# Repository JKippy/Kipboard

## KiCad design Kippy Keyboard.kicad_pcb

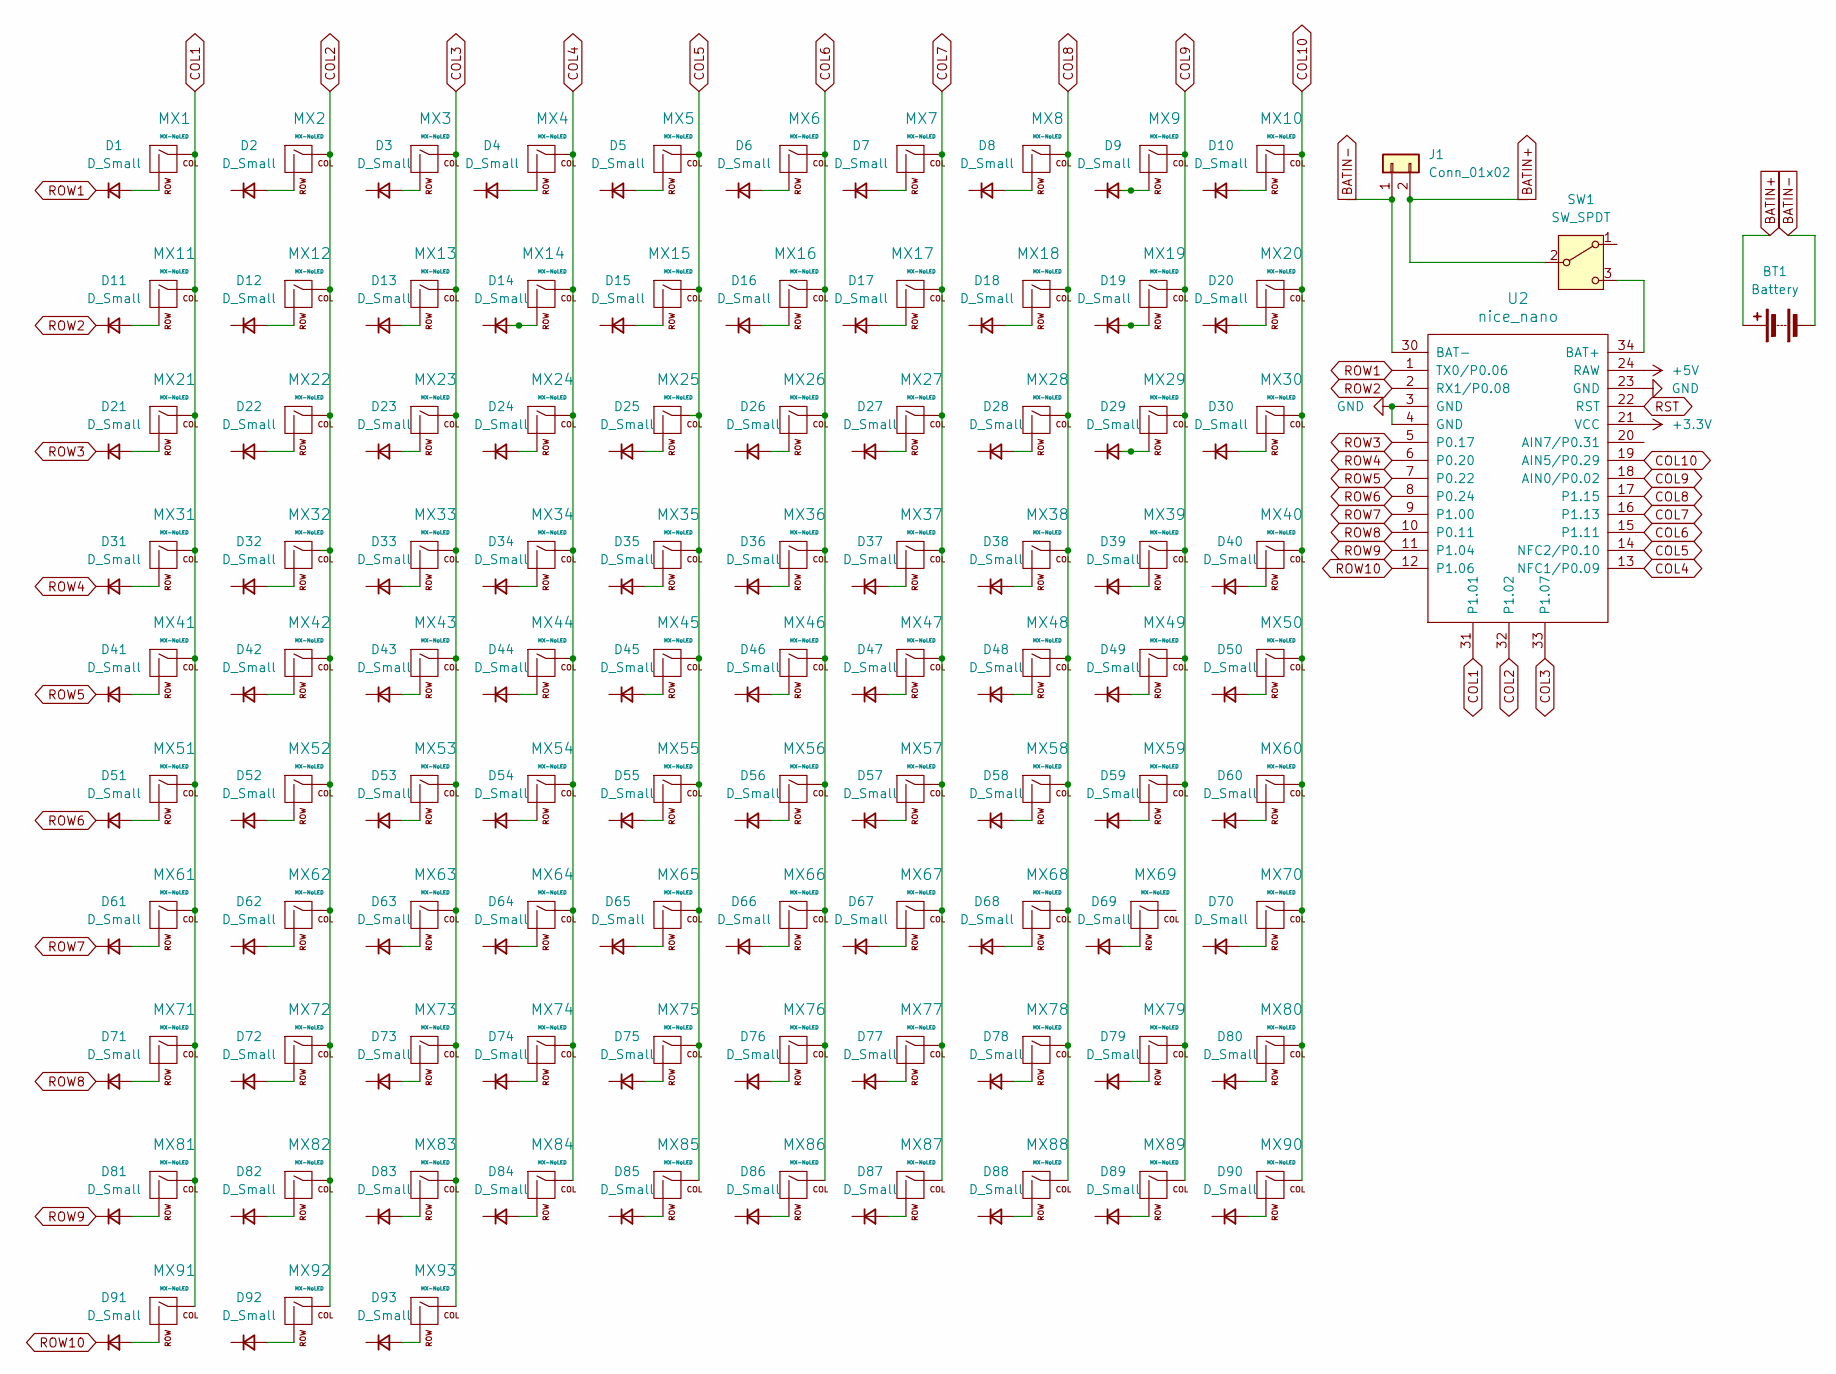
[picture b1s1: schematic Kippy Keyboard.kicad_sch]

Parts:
BT1: Battery
D1, D2, D3, D4, D5, D6, D7, D8, D9, D10, D11, D12, D13, D14, D15, D16, D17, D18, D19, D20, D21, D22, D23, D24, D25, D26, D27, D28, D29, D30, D31, D32, D33, D34, D35, D36, D37, D38, D39, D40, D41, D42, D43, D44, D45, D46, D47, D48, D49, D50, D51, D52, D53, D54, D55, D56, D57, D58, D59, D60, D61, D62, D63, D64, D65, D66, D67, D68, D69, D70, D71, D72, D73, D74, D75, D76, D77, D78, D79, D80, D81, D82, D83, D84, D85, D86, D87, D88, D89, D90, D91, D92, D93: D_Small; D_SOD-123
J1: Conn_01x02; JST_PH_S2B-PH-K_1x02_P2.00mm_Horizontal
MX1, MX2, MX3, MX4, MX5, MX6, MX7, MX8, MX9, MX10, MX11, MX12, MX13, MX14, MX15, MX16, MX17, MX18, MX19, MX20, MX21, MX22, MX23, MX24, MX25, MX26, MX27, MX28, MX29, MX30, MX31, MX32, MX33, MX34, MX35, MX36, MX37, MX38, MX39, MX40, MX41, MX42, MX43, MX44, MX45, MX46, MX47, MX48, MX49, MX50, MX51, MX52, MX53, MX54, MX55, MX56, MX57, MX58, MX59, MX60, MX61, MX62, MX63, MX64, MX65, MX66, MX67, MX68, MX69, MX70, MX71, MX72, MX73, MX74, MX75, MX76, MX77, MX78, MX79, MX80, MX81, MX82, MX83, MX84, MX85, MX86, MX87, MX88, MX89, MX90, MX91, MX92, MX93: MX-NoLED; SW_Hotswap_Kailh_MX_1.00u_3d; MPN CPG151101S11-16
SW1: SW_SPDT; SW_Slide_SPDT_Angled_CK_OS102011MA1Q
U2: nice_nano

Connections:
+3.3V: U2.21 (VCC)
+5V: U2.24 (RAW)
BATIN+: BT1.1 (+), J1.2, SW1.2 (B)
BATIN-: BT1.2 (-), J1.1, U2.30 (BAT-)
COL1: MX1.1 (COL), MX11.1 (COL), MX21.1 (COL), MX31.1 (COL), MX41.1 (COL), MX51.1 (COL), MX61.1 (COL), MX71.1 (COL), MX81.1 (COL), MX91.1 (COL), U2.31 (P1.01)
COL2: MX2.1 (COL), MX12.1 (COL), MX22.1 (COL), MX32.1 (COL), MX42.1 (COL), MX52.1 (COL), MX62.1 (COL), MX72.1 (COL), MX82.1 (COL), MX92.1 (COL), U2.32 (P1.02)
COL3: MX3.1 (COL), MX13.1 (COL), MX23.1 (COL), MX33.1 (COL), MX43.1 (COL), MX53.1 (COL), MX63.1 (COL), MX73.1 (COL), MX83.1 (COL), MX93.1 (COL), U2.33 (P1.07)
COL4: MX4.1 (COL), MX14.1 (COL), MX24.1 (COL), MX34.1 (COL), MX44.1 (COL), MX54.1 (COL), MX64.1 (COL), MX74.1 (COL), MX84.1 (COL), U2.13 (NFC1/P0.09)
COL5: MX5.1 (COL), MX15.1 (COL), MX25.1 (COL), MX35.1 (COL), MX45.1 (COL), MX55.1 (COL), MX65.1 (COL), MX75.1 (COL), MX85.1 (COL), U2.14 (NFC2/P0.10)
COL6: MX6.1 (COL), MX16.1 (COL), MX26.1 (COL), MX36.1 (COL), MX46.1 (COL), MX56.1 (COL), MX66.1 (COL), MX76.1 (COL), MX86.1 (COL), U2.15 (P1.11)
COL7: MX7.1 (COL), MX17.1 (COL), MX27.1 (COL), MX37.1 (COL), MX47.1 (COL), MX57.1 (COL), MX67.1 (COL), MX77.1 (COL), MX87.1 (COL), U2.16 (P1.13)
COL8: MX8.1 (COL), MX18.1 (COL), MX28.1 (COL), MX38.1 (COL), MX48.1 (COL), MX58.1 (COL), MX68.1 (COL), MX78.1 (COL), MX88.1 (COL), U2.17 (P1.15)
COL9: MX9.1 (COL), MX19.1 (COL), MX29.1 (COL), MX39.1 (COL), MX49.1 (COL), MX59.1 (COL), MX79.1 (COL), MX89.1 (COL), U2.18 (AIN0/P0.02)
COL10: MX10.1 (COL), MX20.1 (COL), MX30.1 (COL), MX40.1 (COL), MX50.1 (COL), MX60.1 (COL), MX70.1 (COL), MX80.1 (COL), MX90.1 (COL), U2.19 (AIN5/P0.29)
GND: U2.3 (GND), U2.4 (GND), U2.23 (GND)
unnamed: D1.2 (A), MX1.2 (ROW)
unnamed: D2.2 (A), MX2.2 (ROW)
unnamed: D3.2 (A), MX3.2 (ROW)
unnamed: D4.2 (A), MX4.2 (ROW)
unnamed: D5.2 (A), MX5.2 (ROW)
unnamed: D6.2 (A), MX6.2 (ROW)
unnamed: D7.2 (A), MX7.2 (ROW)
unnamed: D8.2 (A), MX8.2 (ROW)
unnamed: D9.2 (A), MX9.2 (ROW)
unnamed: D10.2 (A), MX10.2 (ROW)
unnamed: D11.2 (A), MX11.2 (ROW)
unnamed: D12.2 (A), MX12.2 (ROW)
unnamed: D13.2 (A), MX13.2 (ROW)
unnamed: D14.2 (A), MX14.2 (ROW)
unnamed: D15.2 (A), MX15.2 (ROW)
unnamed: D16.2 (A), MX16.2 (ROW)
unnamed: D17.2 (A), MX17.2 (ROW)
unnamed: D18.2 (A), MX18.2 (ROW)
unnamed: D19.2 (A), MX19.2 (ROW)
unnamed: D20.2 (A), MX20.2 (ROW)
unnamed: D21.2 (A), MX21.2 (ROW)
unnamed: D22.2 (A), MX22.2 (ROW)
unnamed: D23.2 (A), MX23.2 (ROW)
unnamed: D24.2 (A), MX24.2 (ROW)
unnamed: D25.2 (A), MX25.2 (ROW)
unnamed: D26.2 (A), MX26.2 (ROW)
unnamed: D27.2 (A), MX27.2 (ROW)
unnamed: D28.2 (A), MX28.2 (ROW)
unnamed: D29.2 (A), MX29.2 (ROW)
unnamed: D30.2 (A), MX30.2 (ROW)
unnamed: D31.2 (A), MX31.2 (ROW)
unnamed: D32.2 (A), MX32.2 (ROW)
unnamed: D33.2 (A), MX33.2 (ROW)
unnamed: D34.2 (A), MX34.2 (ROW)
unnamed: D35.2 (A), MX35.2 (ROW)
unnamed: D36.2 (A), MX36.2 (ROW)
unnamed: D37.2 (A), MX37.2 (ROW)
unnamed: D38.2 (A), MX38.2 (ROW)
unnamed: D39.2 (A), MX39.2 (ROW)
unnamed: D40.2 (A), MX40.2 (ROW)
unnamed: D41.2 (A), MX41.2 (ROW)
unnamed: D42.2 (A), MX42.2 (ROW)
unnamed: D43.2 (A), MX43.2 (ROW)
unnamed: D44.2 (A), MX44.2 (ROW)
unnamed: D45.2 (A), MX45.2 (ROW)
unnamed: D46.2 (A), MX46.2 (ROW)
unnamed: D47.2 (A), MX47.2 (ROW)
unnamed: D48.2 (A), MX48.2 (ROW)
unnamed: D49.2 (A), MX49.2 (ROW)
unnamed: D50.2 (A), MX50.2 (ROW)
unnamed: D51.2 (A), MX51.2 (ROW)
unnamed: D52.2 (A), MX52.2 (ROW)
unnamed: D53.2 (A), MX53.2 (ROW)
unnamed: D54.2 (A), MX54.2 (ROW)
unnamed: D55.2 (A), MX55.2 (ROW)
unnamed: D56.2 (A), MX56.2 (ROW)
unnamed: D57.2 (A), MX57.2 (ROW)
unnamed: D58.2 (A), MX58.2 (ROW)
unnamed: D59.2 (A), MX59.2 (ROW)
unnamed: D60.2 (A), MX60.2 (ROW)
unnamed: D61.2 (A), MX61.2 (ROW)
unnamed: D62.2 (A), MX62.2 (ROW)
unnamed: D63.2 (A), MX63.2 (ROW)
unnamed: D64.2 (A), MX64.2 (ROW)
unnamed: D65.2 (A), MX65.2 (ROW)
unnamed: D66.2 (A), MX66.2 (ROW)
unnamed: D67.2 (A), MX67.2 (ROW)
unnamed: D68.2 (A), MX68.2 (ROW)
unnamed: D69.2 (A), MX69.2 (ROW)
unnamed: D70.2 (A), MX70.2 (ROW)
unnamed: D71.2 (A), MX71.2 (ROW)
unnamed: D72.2 (A), MX72.2 (ROW)
unnamed: D73.2 (A), MX73.2 (ROW)
unnamed: D74.2 (A), MX74.2 (ROW)
unnamed: D75.2 (A), MX75.2 (ROW)
unnamed: D76.2 (A), MX76.2 (ROW)
unnamed: D77.2 (A), MX77.2 (ROW)
unnamed: D78.2 (A), MX78.2 (ROW)
unnamed: D79.2 (A), MX79.2 (ROW)
unnamed: D80.2 (A), MX80.2 (ROW)
unnamed: D81.2 (A), MX81.2 (ROW)
unnamed: D82.2 (A), MX82.2 (ROW)
unnamed: D83.2 (A), MX83.2 (ROW)
unnamed: D84.2 (A), MX84.2 (ROW)
unnamed: D85.2 (A), MX85.2 (ROW)
unnamed: D86.2 (A), MX86.2 (ROW)
unnamed: D87.2 (A), MX87.2 (ROW)
unnamed: D88.2 (A), MX88.2 (ROW)
unnamed: D89.2 (A), MX89.2 (ROW)
unnamed: D90.2 (A), MX90.2 (ROW)
unnamed: D91.2 (A), MX91.2 (ROW)
unnamed: D92.2 (A), MX92.2 (ROW)
unnamed: D93.2 (A), MX93.2 (ROW)
unnamed: SW1.3 (C), U2.34 (BAT+)
ROW1: D1.1 (K), U2.1 (TX0/P0.06)
ROW2: D11.1 (K), U2.2 (RX1/P0.08)
ROW3: D21.1 (K), U2.5 (P0.17)
ROW4: D31.1 (K), U2.6 (P0.20)
ROW5: D41.1 (K), U2.7 (P0.22)
ROW6: D51.1 (K), U2.8 (P0.24)
ROW7: D61.1 (K), U2.9 (P1.00)
ROW8: D71.1 (K), U2.10 (P0.11)
ROW9: D81.1 (K), U2.11 (P1.04)
ROW10: D91.1 (K), U2.12 (P1.06)
RST: U2.22 (RST)

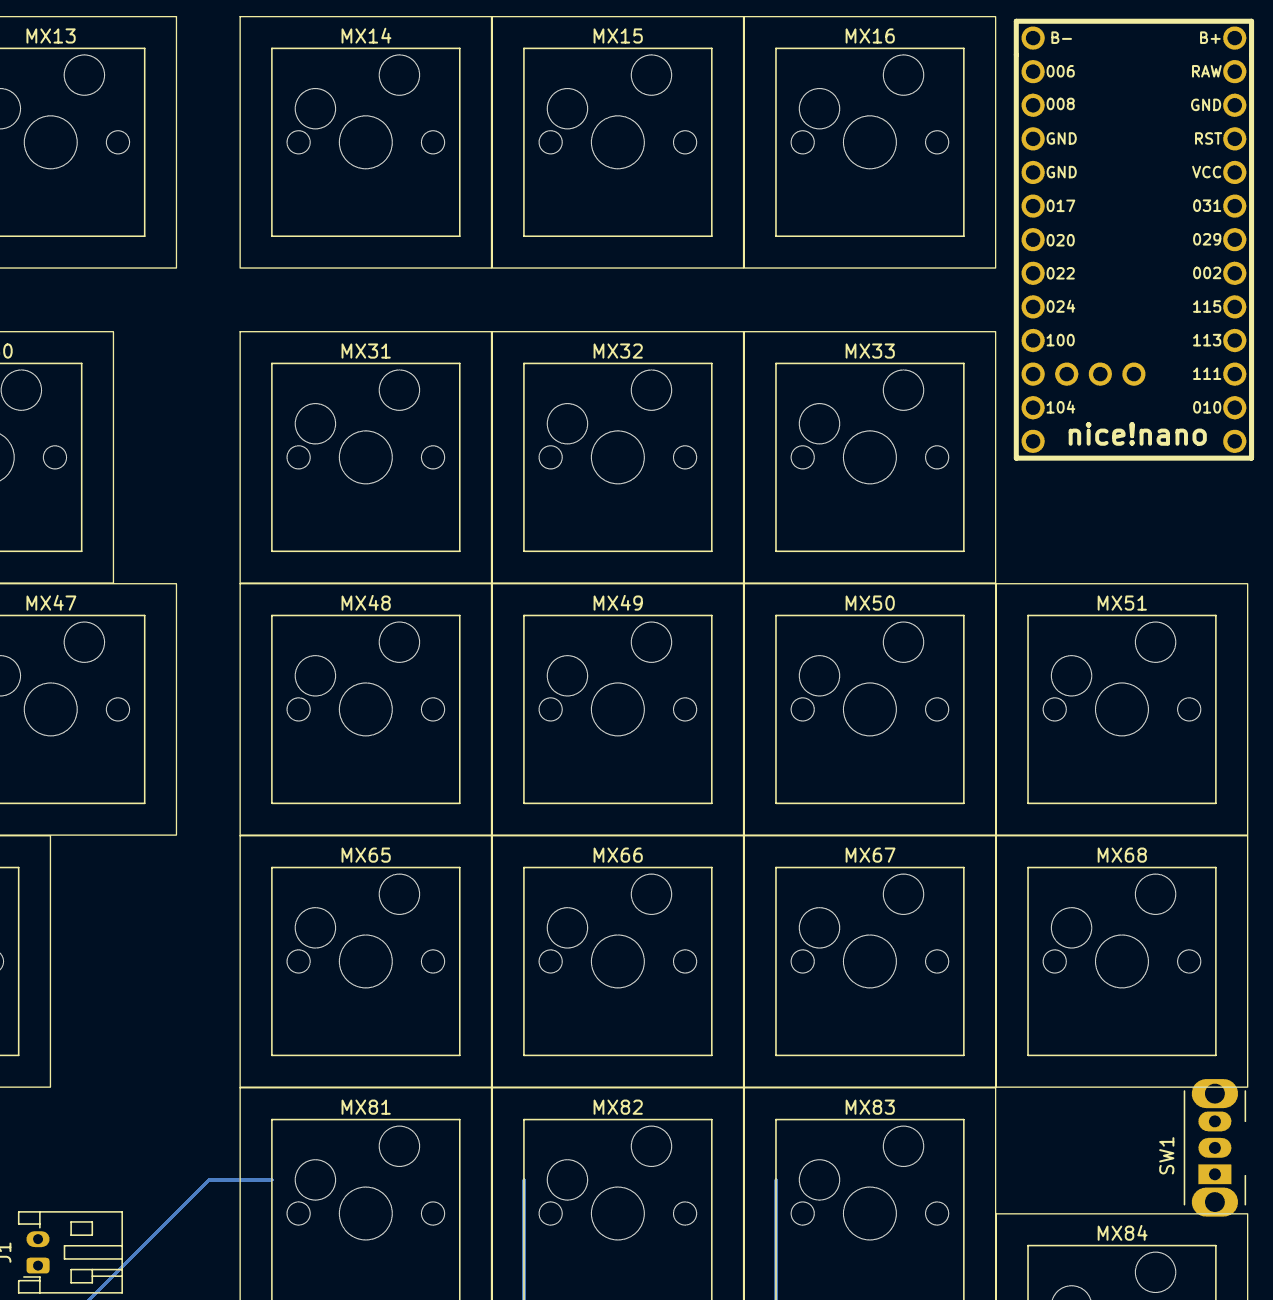
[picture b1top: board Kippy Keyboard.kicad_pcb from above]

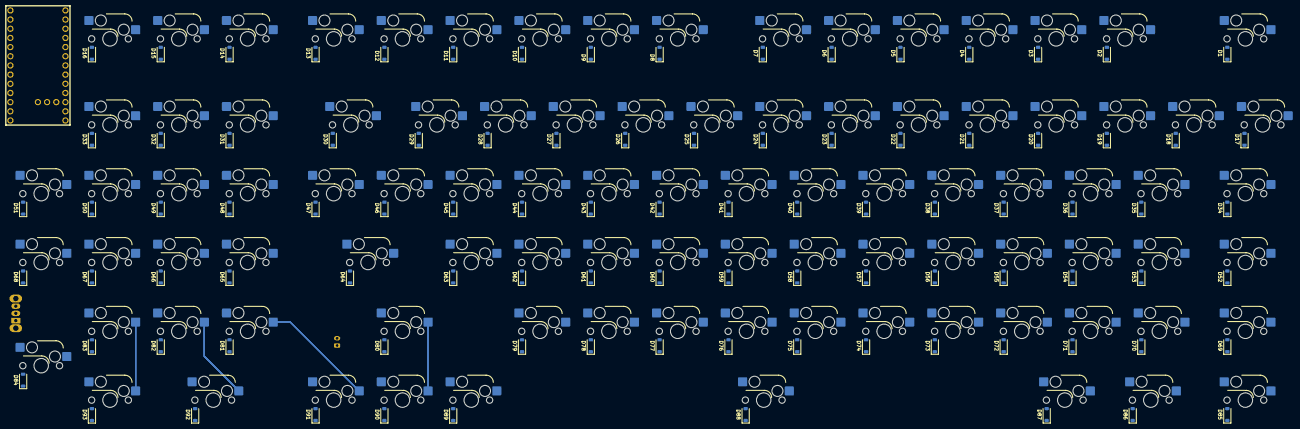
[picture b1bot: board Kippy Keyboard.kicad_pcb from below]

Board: 2 copper layers, 189 parts (93 on the bottom side), 117 nets.

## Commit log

2025-05-28 init commit
